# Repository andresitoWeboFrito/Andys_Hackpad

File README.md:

# Andys_Hackpad
My own version of the macropad tutorial. It comes with 11 funtiion keys, an OLED Screen and an Encoder to use as volume / slider controls. All of this powered with a XIAO RP2040 microcontroller.

## Features
* 11 Mechanical switches
* 1 EC11 Rotary encoder
* 1 128x32px OLED display
* A custom 3d printed case

## CAD
The case was designed using OnShape. It is assembled together using 4 M3 screws and its mating heatset inserts.
The screws are inserted from the bottom of the case and screwed to the top part of the case.
The PCB sits in the middle so it becomes sandwiched between the top and the bottom part of the case.

There are only 2 pieces for the case. The top part and the bottom part.

## PCB & Schematic

This is the schematic of the Board. It was made with KiCad.

This is the PCB Layout. It was also made in KiCad. The hackclub logo was imported as an .svg to the silkscreen layer.
It has a ground plane on the bottom layer, and a slightly thicker traces as KiCad defaults.

## Firmware
At the moment the firmware wouldn't work. Im waiting to assemble it and test it before updating it.

## BOM
This is the list of what you'll need to build it! :)
* 11x Cherry MX Switches
* 12x 1N4148 DO-35 Diodes
* 1x 0.91" 128x32 OLED Display
* 1x EC11 Rotary Encoder
* 1x XIAO RP2040
* 9x 1u Cherry caps
* 2x 1,5u Cherry caps
* 4x M3 Heatset inserts
* 2x M3x18mm screws
* 2x M3x16mm screws 
* Printed case parts

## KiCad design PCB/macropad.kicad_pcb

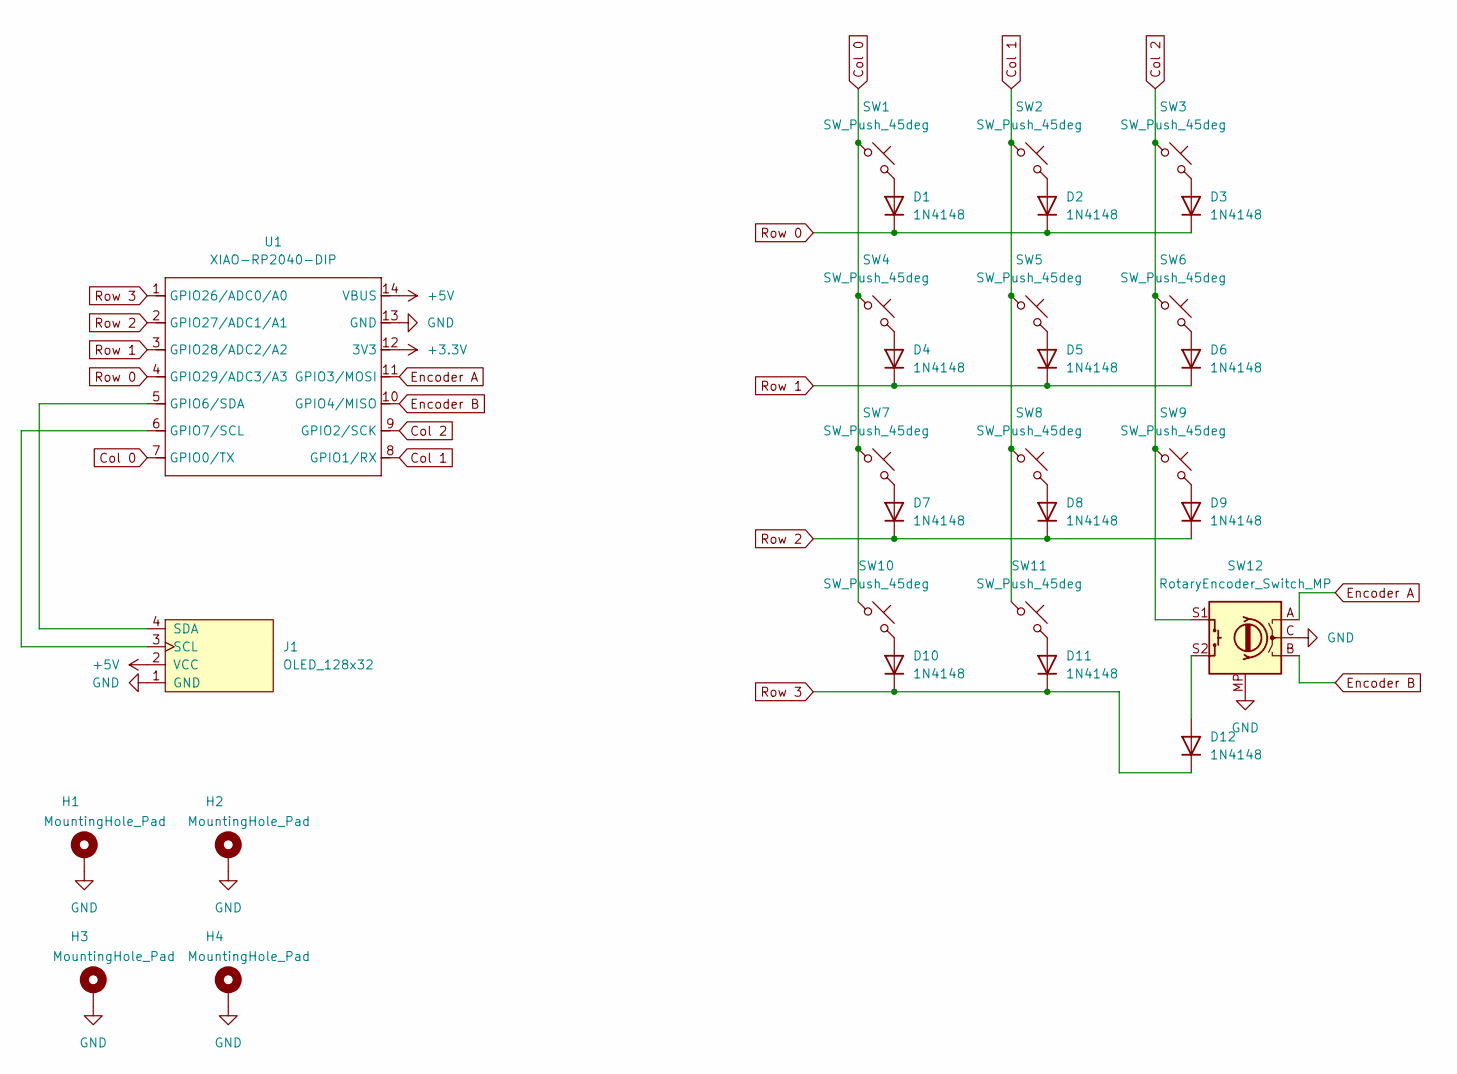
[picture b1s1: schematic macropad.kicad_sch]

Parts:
D1, D2, D3, D4, D5, D6, D7, D8, D9, D10, D11, D12: 1N4148; D_DO-35_SOD27_P7.62mm_Horizontal
H1, H2, H3, H4: MountingHole_Pad; MountingHole_3.2mm_M3_DIN965_Pad
J1: OLED_128x32
SW1, SW2, SW3, SW4, SW5, SW6, SW7, SW8, SW9, SW10, SW11: SW_Push_45deg; MX_PCB_1.00u
SW12: RotaryEncoder_Switch_MP; Encoder_EC11_MX
U1: XIAO-RP2040-DIP

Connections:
+3.3V: U1.12 (3V3)
+5V: J1.2 (VCC), U1.14 (VBUS)
Col 0: SW1.1, SW4.1, SW7.1, SW10.1, U1.7 (GPIO0/TX)
Col 1: SW2.1, SW5.1, SW8.1, SW11.1, U1.8 (GPIO1/RX)
Col 2: SW3.1, SW6.1, SW9.1, SW12.S1, U1.9 (GPIO2/SCK)
Encoder A: SW12.A, U1.11 (GPIO3/MOSI)
Encoder B: SW12.B, U1.10 (GPIO4/MISO)
GND: H1.1, H2.1, H3.1, H4.1, J1.1 (GND), SW12.C, SW12.MP, U1.13 (GND)
unnamed: D1.2 (A), SW1.2
unnamed: D2.2 (A), SW2.2
unnamed: D3.2 (A), SW3.2
unnamed: D4.2 (A), SW4.2
unnamed: D5.2 (A), SW5.2
unnamed: D6.2 (A), SW6.2
unnamed: D7.2 (A), SW7.2
unnamed: D8.2 (A), SW8.2
unnamed: D9.2 (A), SW9.2
unnamed: D10.2 (A), SW10.2
unnamed: D11.2 (A), SW11.2
unnamed: D12.2 (A), SW12.S2
unnamed: J1.3 (SCL), U1.6 (GPIO7/SCL)
unnamed: J1.4 (SDA), U1.5 (GPIO6/SDA)
Row 0: D1.1 (K), D2.1 (K), D3.1 (K), U1.4 (GPIO29/ADC3/A3)
Row 1: D4.1 (K), D5.1 (K), D6.1 (K), U1.3 (GPIO28/ADC2/A2)
Row 2: D7.1 (K), D8.1 (K), D9.1 (K), U1.2 (GPIO27/ADC1/A1)
Row 3: D10.1 (K), D11.1 (K), D12.1 (K), U1.1 (GPIO26/ADC0/A0)

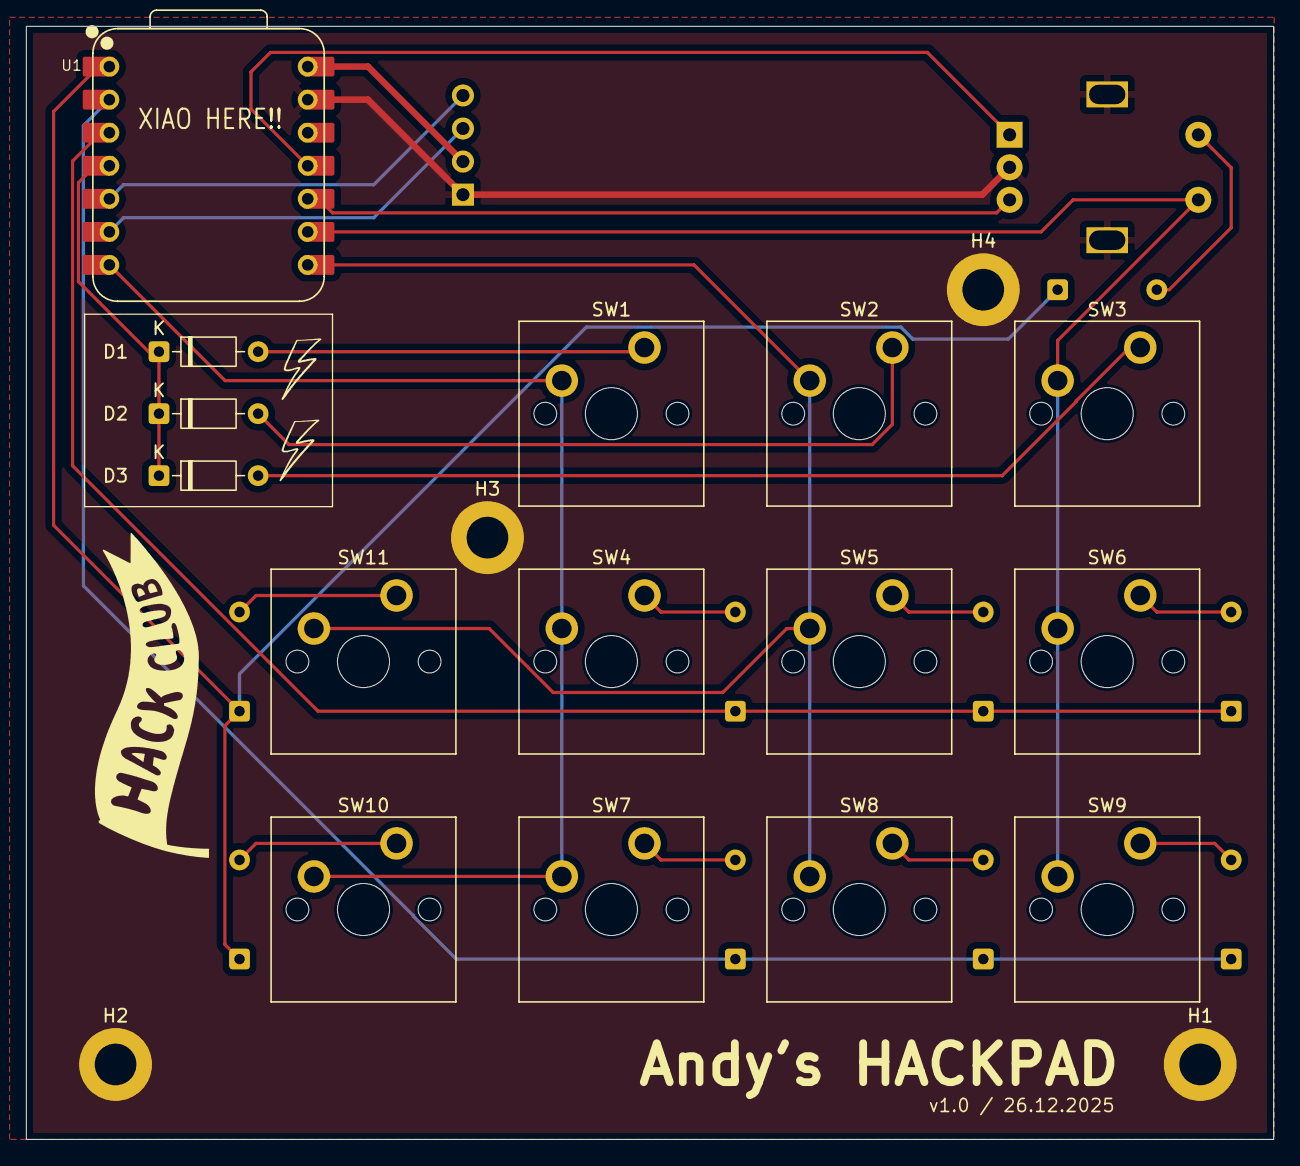
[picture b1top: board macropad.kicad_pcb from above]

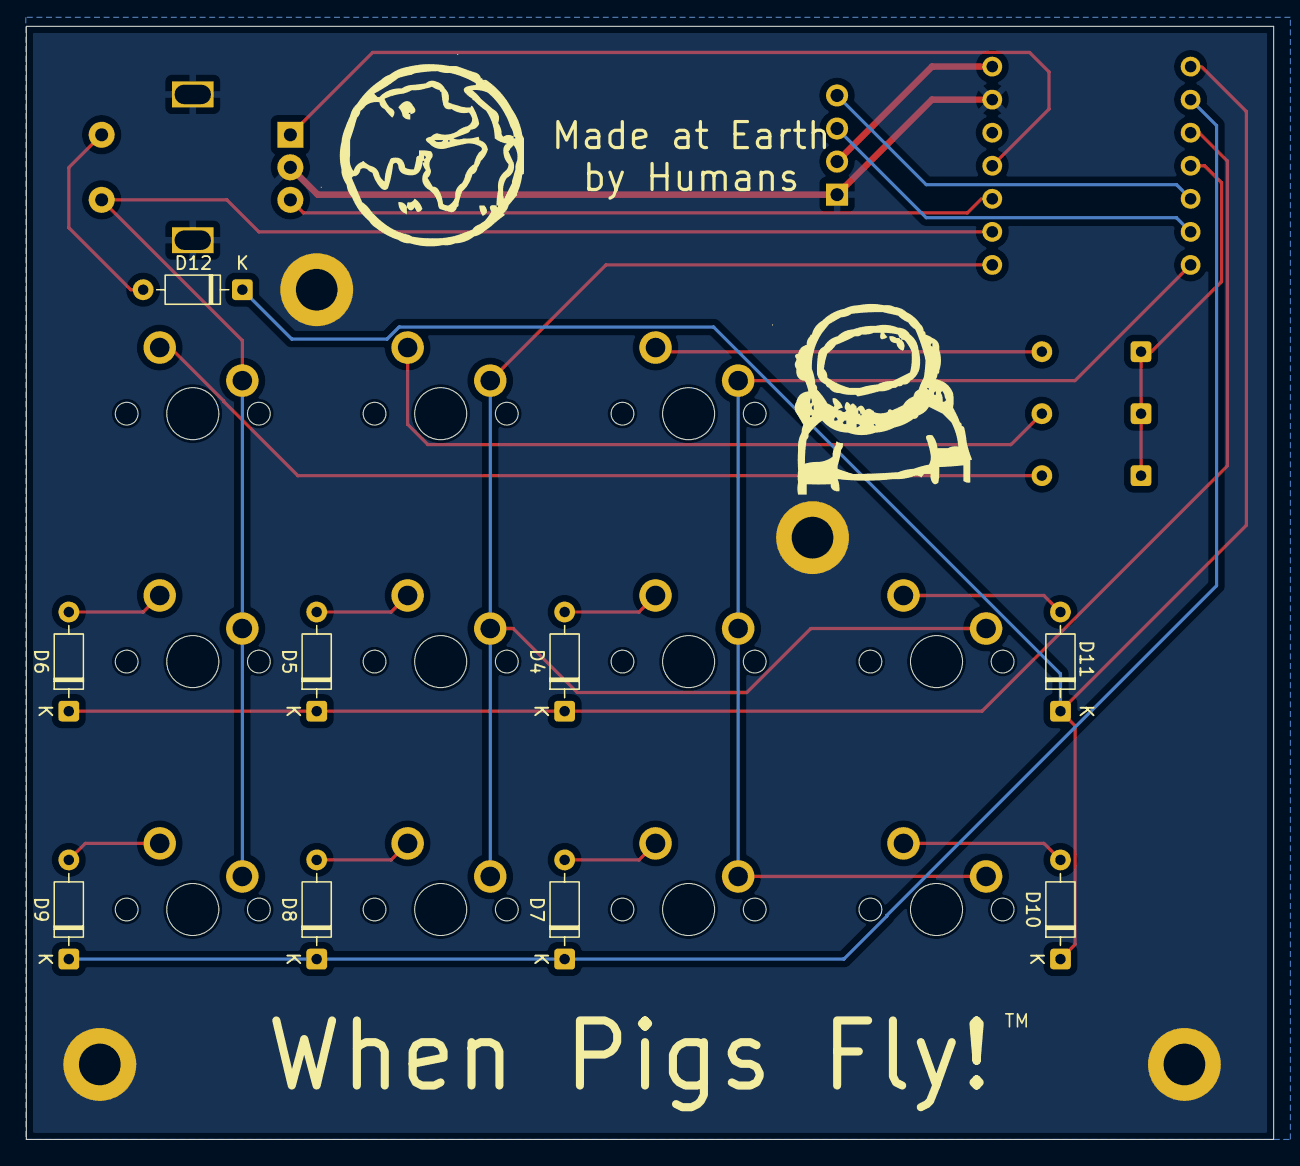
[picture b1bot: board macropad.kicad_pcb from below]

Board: 2 copper layers, 95.8 x 85.5 mm, 30 parts (9 on the bottom side), 25 nets.

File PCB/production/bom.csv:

Designator,Footprint,Quantity,Value,LCSC Part #
"D1, D10, D11, D12, D2, D3, D4, D5, D6, D7, D8, D9",D_DO-35_SOD27_P7.62mm_Horizontal,12,1N4148,
J1,OLED_128x32,1,OLED_128x32,
"SW1, SW10, SW11, SW2, SW3, SW4, SW5, SW6, SW7, SW8, SW9",MX_PCB_1.00u,11,SW_Push_45deg,
SW12,Encoder_EC11_MX,1,RotaryEncoder_Switch_MP,
U1,XIAO-RP2040-DIP,1,XIAO-RP2040-DIP,

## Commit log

2025-12-28 changed readme
2025-12-28 Added project files for revision
2025-12-28 add img exploded view
2025-12-29 requested changes
2026-01-21 new version of the pcb
2026-01-22 new pcb graphics
2026-03-23 defaultish keyboard
2026-03-24 first working sw
2026-03-29 screen turned on!
2026-04-08 basic encoder
2026-04-08 changes to the keymap
2026-04-14 por fin el puto bongocat
2026-05-17 corrected bongocats frames
